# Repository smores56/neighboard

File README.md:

The Neighboard
==============

_coming soon!_

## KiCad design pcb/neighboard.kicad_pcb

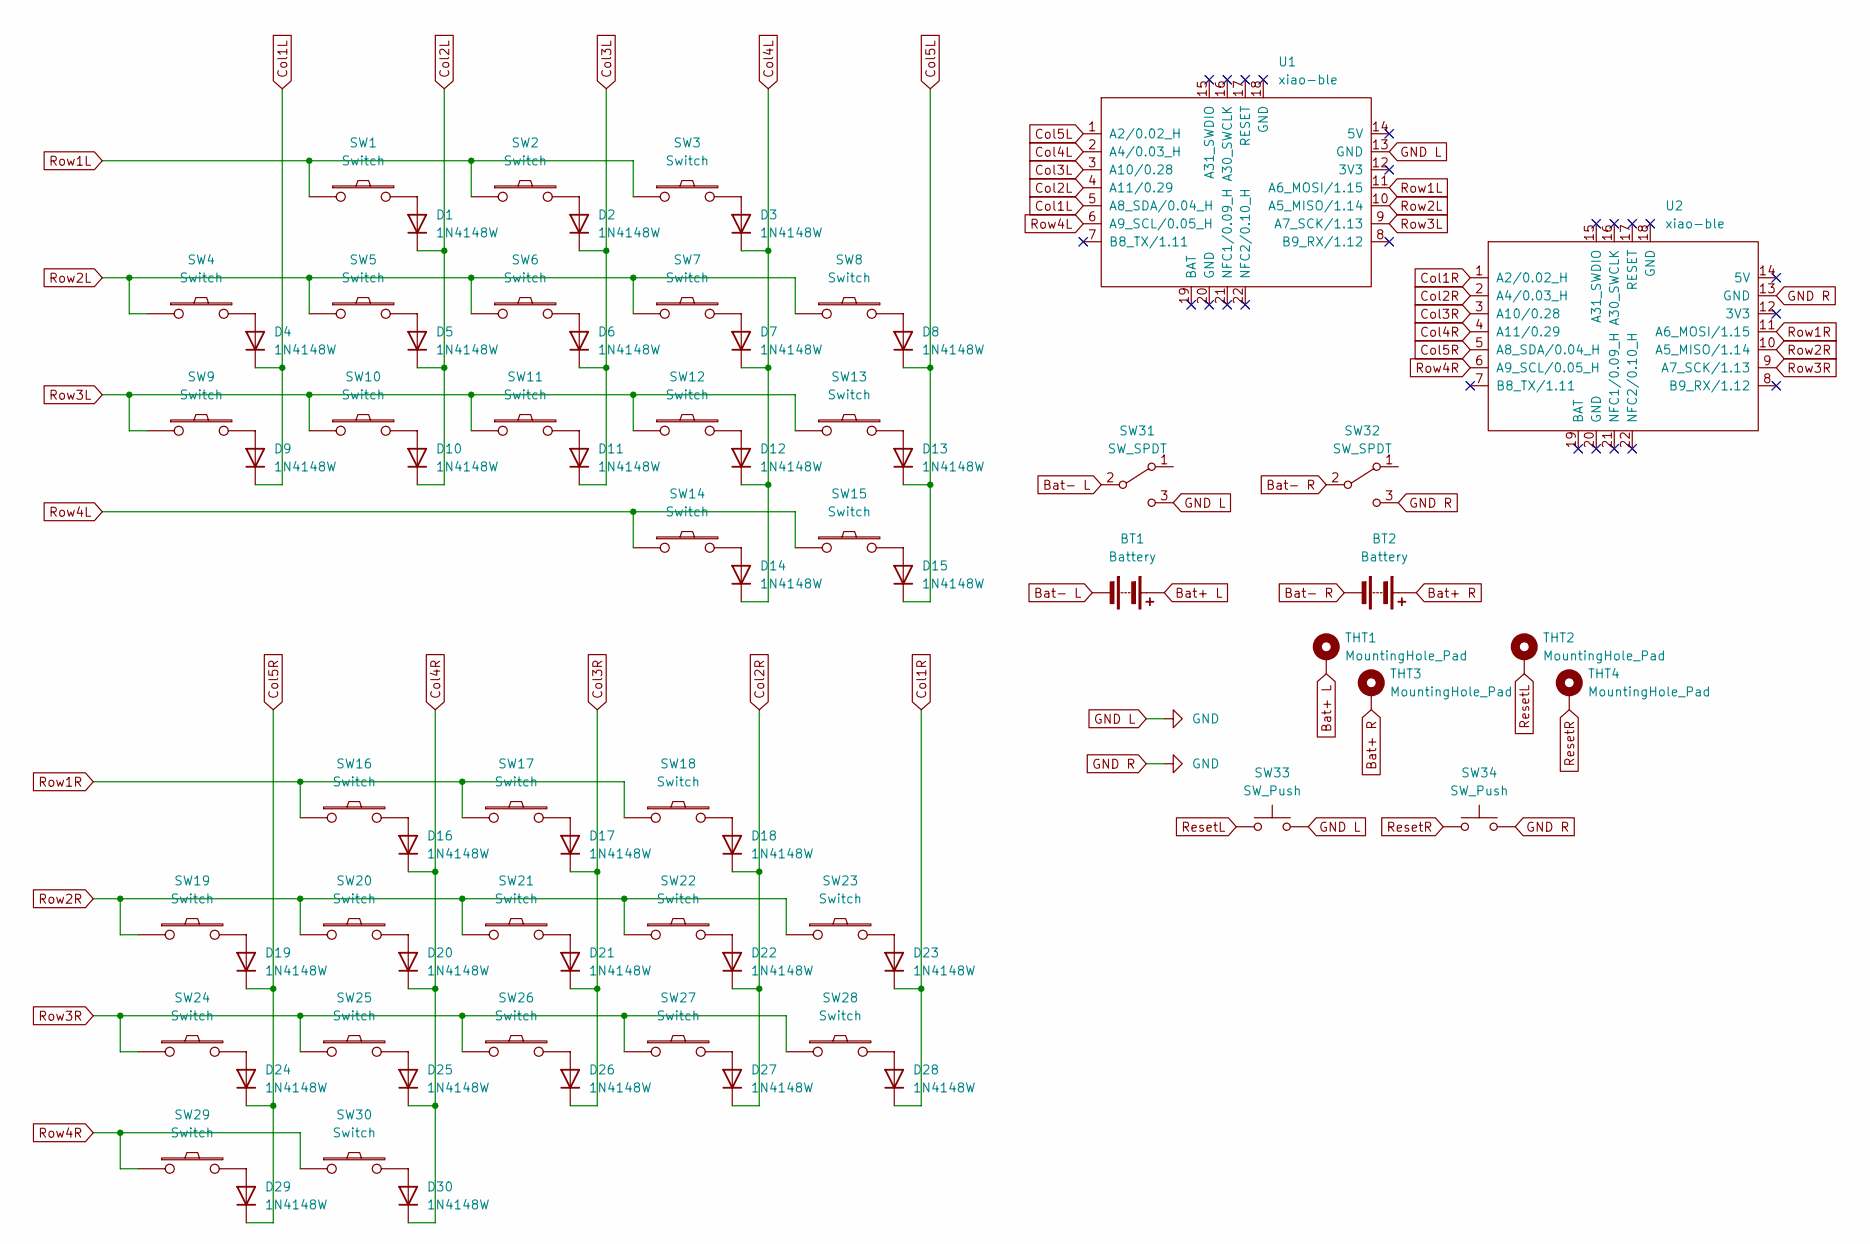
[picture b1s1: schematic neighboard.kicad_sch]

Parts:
BT1, BT2: Battery; aa2-1017-battery-holder
D1, D2, D3, D4, D5, D6, D7, D8, D9, D10, D11, D12, D13, D14, D15, D16, D17, D18, D19, D20, D21, D22, D23, D24, D25, D26, D27, D28, D29, D30: 1N4148W; smd-diode
SW1, SW2, SW3, SW4, SW5, SW6, SW7, SW8, SW9, SW10, SW11, SW12, SW13, SW14, SW15, SW16, SW17, SW18, SW19, SW20, SW21, SW22, SW23, SW24, SW25, SW26, SW27, SW28, SW29, SW30: Switch; choc-switch-one-sided
SW31, SW32: SW_SPDT; power-switch
SW33, SW34: SW_Push; reset-switch-angled-4pin
THT1, THT2, THT3, THT4: MountingHole_Pad; pogo-pin-ultra-low
U1, U2: xiao-ble; xiao-ble-simple

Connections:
Bat+ L: BT1.1 (+), THT1.1
Bat+ R: BT2.1 (+), THT3.1
Bat- L: BT1.2 (-), SW31.2 (B)
Bat- R: BT2.2 (-), SW32.2 (B)
Col1L: D4.1 (K), D9.1 (K), U1.5 (A8_SDA/0.04_H)
Col1R: D23.1 (K), D28.1 (K), U2.1 (A2/0.02_H)
Col2L: D1.1 (K), D5.1 (K), D10.1 (K), U1.4 (A11/0.29)
Col2R: D18.1 (K), D22.1 (K), D27.1 (K), U2.2 (A4/0.03_H)
Col3L: D2.1 (K), D6.1 (K), D11.1 (K), U1.3 (A10/0.28)
Col3R: D17.1 (K), D21.1 (K), D26.1 (K), U2.3 (A10/0.28)
Col4L: D3.1 (K), D7.1 (K), D12.1 (K), D14.1 (K), U1.2 (A4/0.03_H)
Col4R: D16.1 (K), D20.1 (K), D25.1 (K), D30.1 (K), U2.4 (A11/0.29)
Col5L: D8.1 (K), D13.1 (K), D15.1 (K), U1.1 (A2/0.02_H)
Col5R: D19.1 (K), D24.1 (K), D29.1 (K), U2.5 (A8_SDA/0.04_H)
GND L: SW31.3 (C), SW32.3 (C), SW33.2, SW34.2, U1.13 (GND), U2.13 (GND)
unnamed: D1.2 (A), SW1.2
unnamed: D2.2 (A), SW2.2
unnamed: D3.2 (A), SW3.2
unnamed: D4.2 (A), SW4.2
unnamed: D5.2 (A), SW5.2
unnamed: D6.2 (A), SW6.2
unnamed: D7.2 (A), SW7.2
unnamed: D8.2 (A), SW8.2
unnamed: D9.2 (A), SW9.2
unnamed: D10.2 (A), SW10.2
unnamed: D11.2 (A), SW11.2
unnamed: D12.2 (A), SW12.2
unnamed: D13.2 (A), SW13.2
unnamed: D14.2 (A), SW14.2
unnamed: D15.2 (A), SW15.2
unnamed: D16.2 (A), SW16.2
unnamed: D17.2 (A), SW17.2
unnamed: D18.2 (A), SW18.2
unnamed: D19.2 (A), SW19.2
unnamed: D20.2 (A), SW20.2
unnamed: D21.2 (A), SW21.2
unnamed: D22.2 (A), SW22.2
unnamed: D23.2 (A), SW23.2
unnamed: D24.2 (A), SW24.2
unnamed: D25.2 (A), SW25.2
unnamed: D26.2 (A), SW26.2
unnamed: D27.2 (A), SW27.2
unnamed: D28.2 (A), SW28.2
unnamed: D29.2 (A), SW29.2
unnamed: D30.2 (A), SW30.2
ResetL: SW33.1, THT2.1
ResetR: SW34.1, THT4.1
Row1L: SW1.1, SW2.1, SW3.1, U1.11 (A6_MOSI/1.15)
Row1R: SW16.1, SW17.1, SW18.1, U2.11 (A6_MOSI/1.15)
Row2L: SW4.1, SW5.1, SW6.1, SW7.1, SW8.1, U1.10 (A5_MISO/1.14)
Row2R: SW19.1, SW20.1, SW21.1, SW22.1, SW23.1, U2.10 (A5_MISO/1.14)
Row3L: SW9.1, SW10.1, SW11.1, SW12.1, SW13.1, U1.9 (A7_SCK/1.13)
Row3R: SW24.1, SW25.1, SW26.1, SW27.1, SW28.1, U2.9 (A7_SCK/1.13)
Row4L: SW14.1, SW15.1, U1.6 (A9_SCL/0.05_H)
Row4R: SW29.1, SW30.1, U2.6 (A9_SCL/0.05_H)

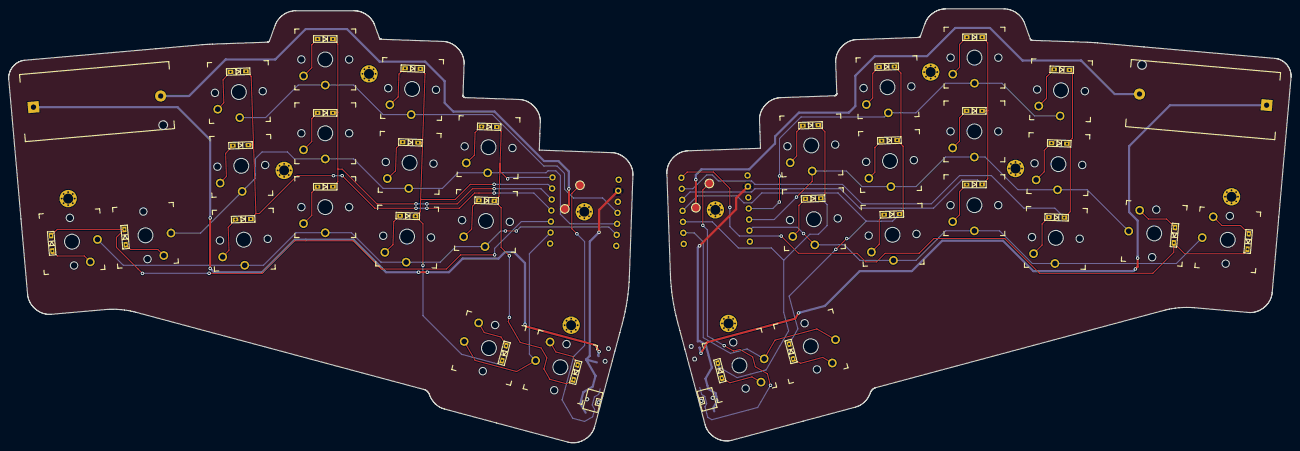
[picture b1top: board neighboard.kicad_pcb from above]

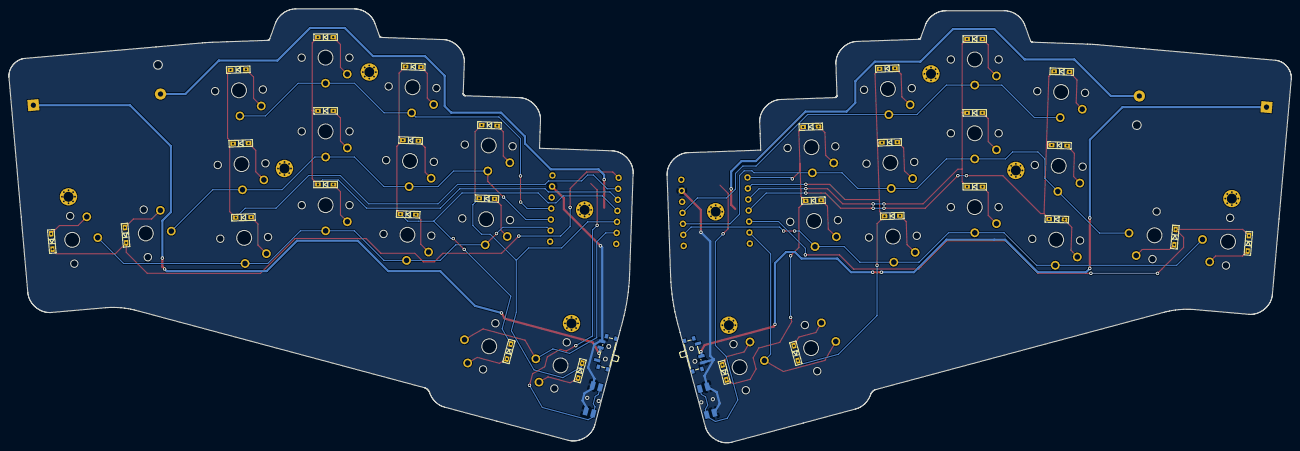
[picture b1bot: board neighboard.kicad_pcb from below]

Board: 2 copper layers, 295.3 x 99.9 mm, 82 parts (2 on the bottom side), 55 nets.

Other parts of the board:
Ref**: Val**; m2-hole
Ref**#2, Ref**#3, Ref**#4, Ref**#5, Ref**#6, Ref**#7, Ref**#8, Ref**#9, Ref**#10: Val**; m2-hole

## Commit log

2023-09-23 Add Ground Fill
2023-09-24 Add Mounting Holes
2024-01-02 Scratch work
